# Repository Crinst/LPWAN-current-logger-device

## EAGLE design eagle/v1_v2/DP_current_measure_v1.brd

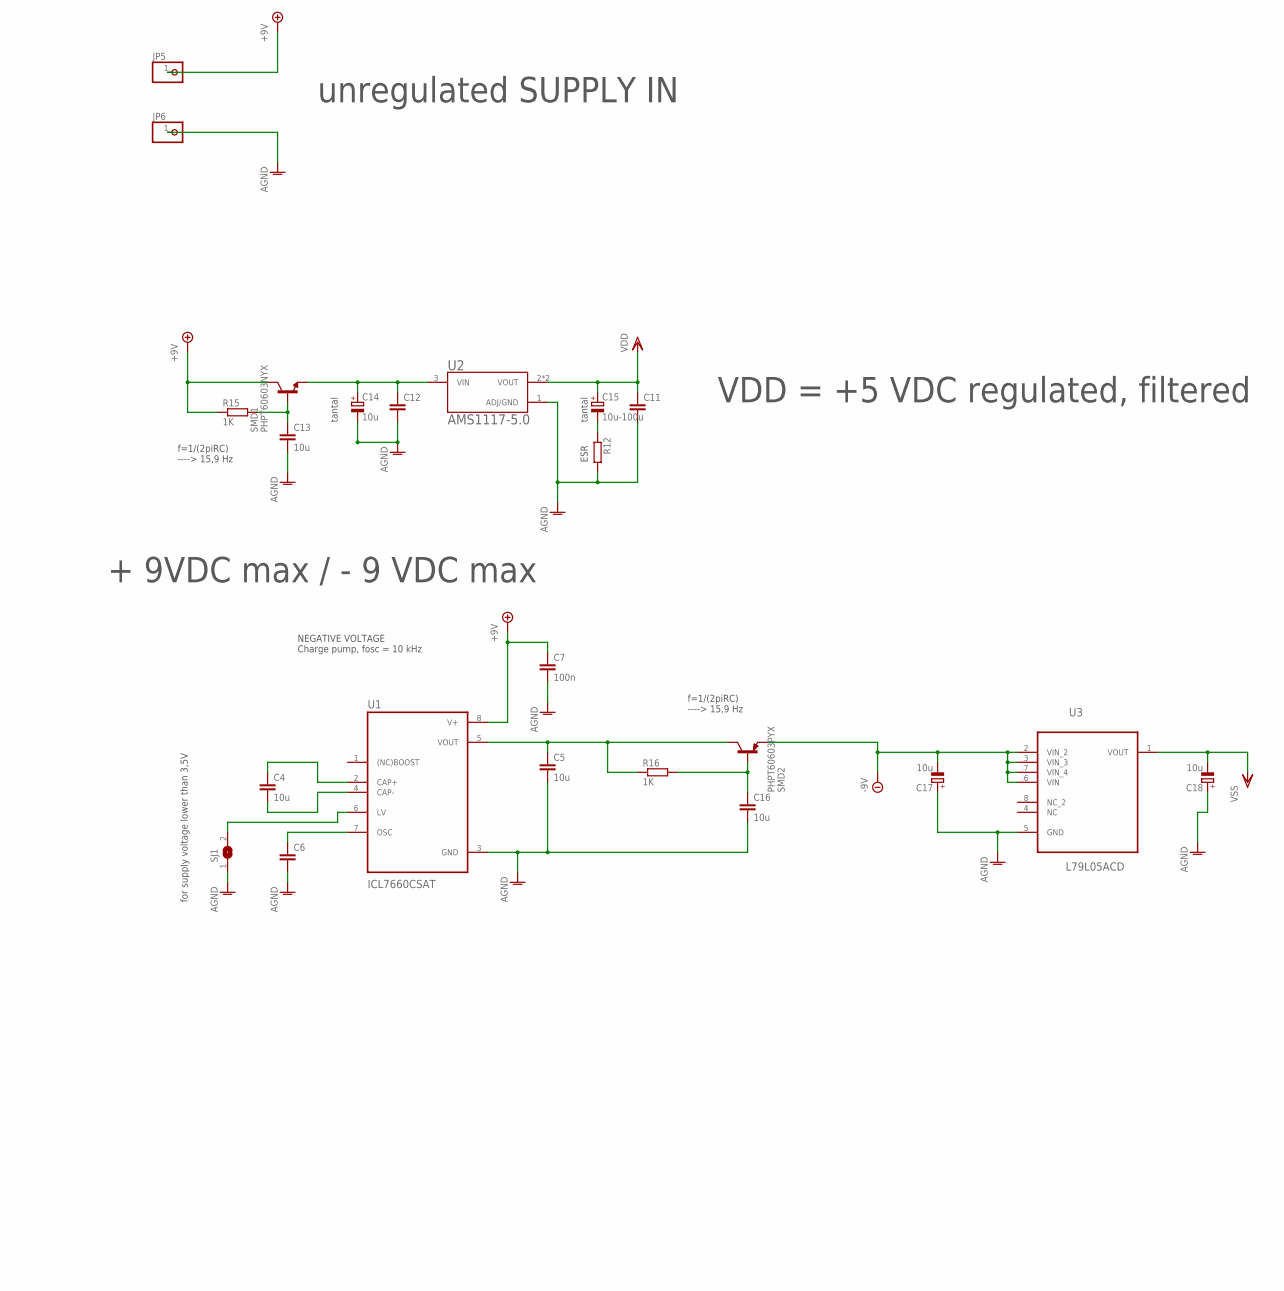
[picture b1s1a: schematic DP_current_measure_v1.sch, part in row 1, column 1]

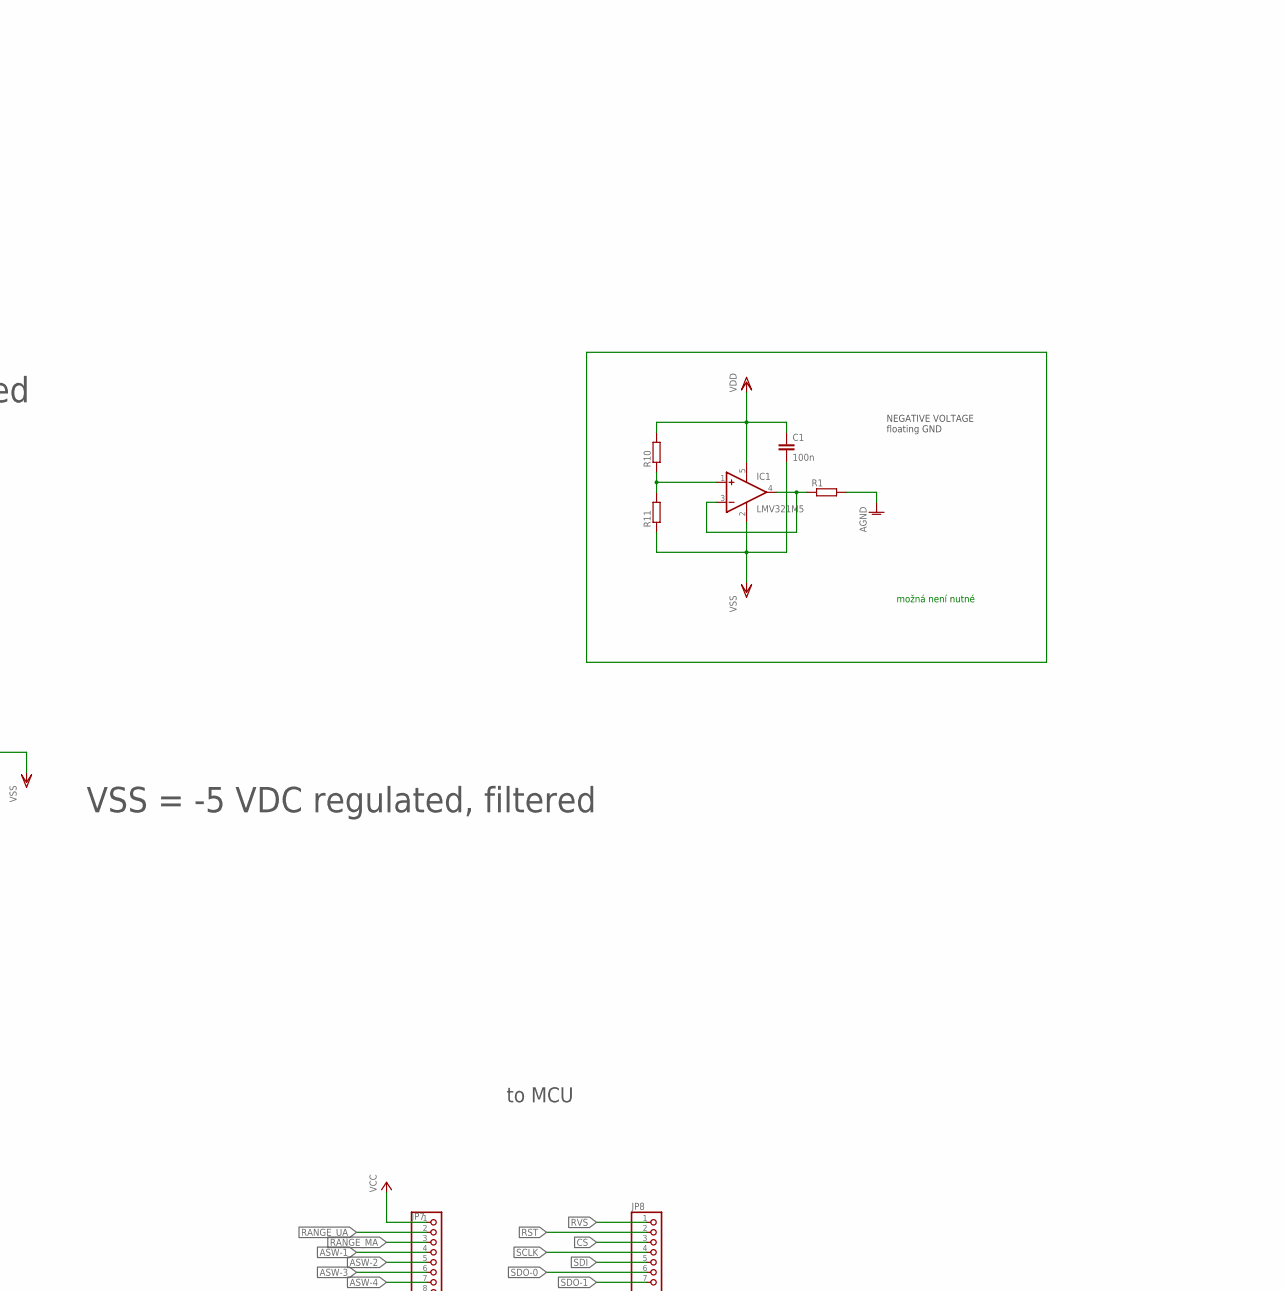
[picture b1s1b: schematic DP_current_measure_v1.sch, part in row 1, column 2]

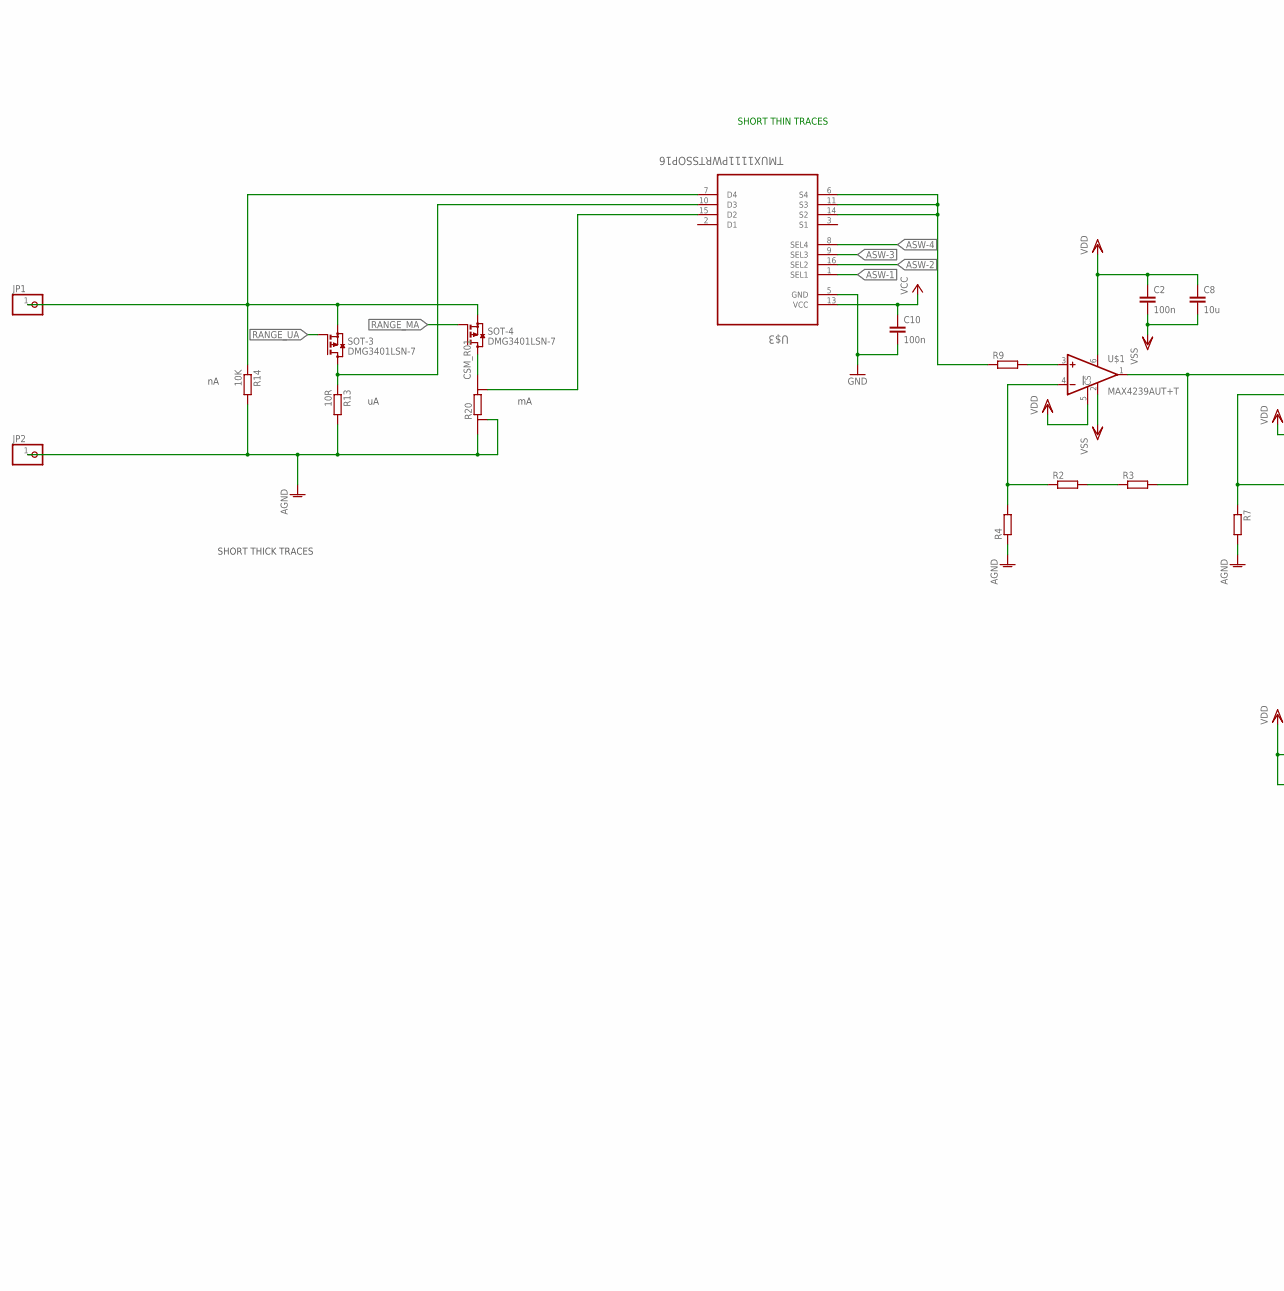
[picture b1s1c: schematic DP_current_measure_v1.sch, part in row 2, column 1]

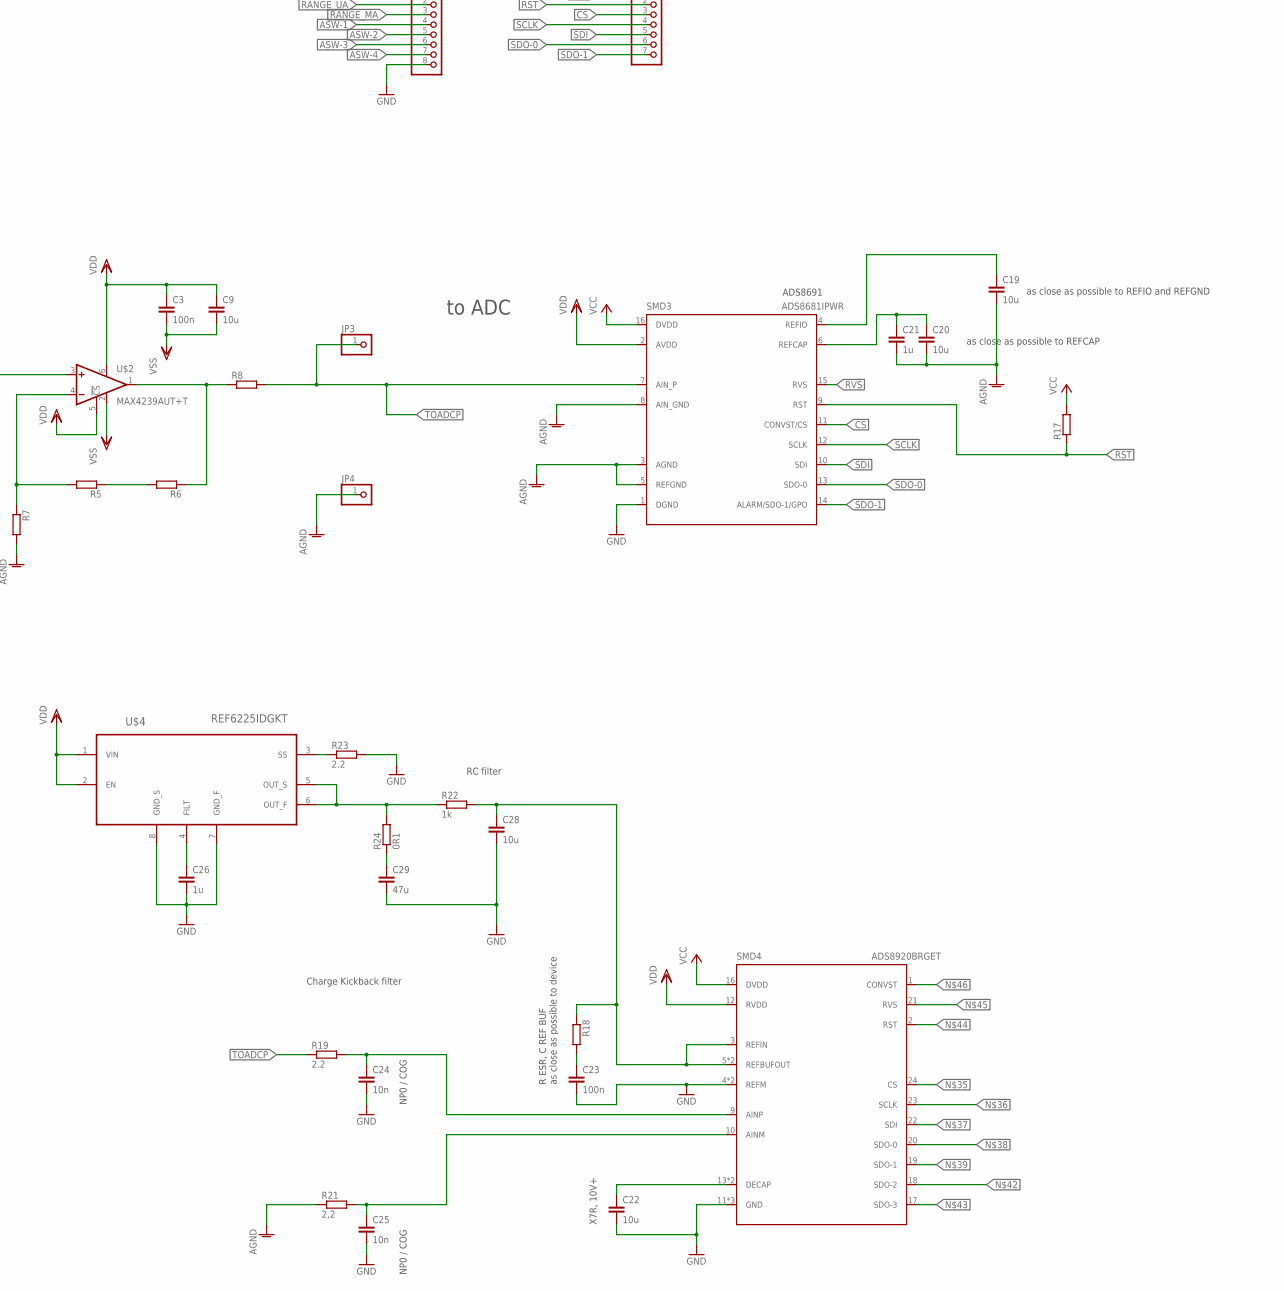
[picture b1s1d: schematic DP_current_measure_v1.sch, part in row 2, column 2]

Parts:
C1, C2, C3, C7, C10, C23: 100n; C0805
C4, C5, C8, C9, C13, C16, C19, C20, C22, C28: 10u; C1206
C6, C11, C12: C-EUC1206; C1206
C14, C17, C18: 10u; SMC_B
C15: 10u-100u; SMC_B
C21: 1u; C0805
C24, C25: 10n; C0805
C26: 1u; C1206
C29: 47u; C1206
IC1: LMV321M5; SOT23-5
JP1, JP2, JP3, JP4, JP5, JP6: PINHD-1X1; 1X01
JP7: PINHD-1X8; 1X08
JP8: PINHD-1X7; 1X07
R1, R2, R3, R4, R5, R6, R7, R8, R9, R10, R11, R12, R17, R18: R-EU_R0805; R0805
R13: 10R; R0805
R14: 10K; R0805
R15, R16: 1K; R0805
R19, R23: 2.2; R0805
R20: CSM_R01; R2512
R21: 2,2; R0805
R22: 1k; R0805
R24: 0R1; R0805
SJ1: SJ
SMD1: PHPT60603NYX; TO127P600X120-5N
SMD2: PHPT60603PYX; TO127P600X120-5N
SMD3: ADS8681IPWR; SOP65P640X120-16N
SMD4: ADS8920BRGET; BQ24195RGER
SOT-3, SOT-4: DMG3401LSN-7; SOT23
U1: ICL7660CSAT; SOIC127P600X175-8N
U2: AMS1117-5.0; SOT229P700X180-4N
U3: L79L05ACD; SOIC127P600X175-8N
U$1, U$2: MAX4239AUT+T; SOT23-6
U$3: TMUX1111PWRTSSOP16; SOP65P640X110-16N
U$4: REF6225IDGKT; SOP65P640X120-16N

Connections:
+9V: JP5.1
+12V: C7.1, R15.1, SMD1.5 (C), U1.8 (V+)
-12V: C17.-, SMD2.1 (E), SMD2.2 (E), SMD2.3 (E), U3.2 (VIN_2), U3.3 (VIN_3), U3.6 (VIN), U3.7 (VIN_4)
AGND: C5.2, C6.2, C7.2, C11.2, C12.2, C13.2, C14.-, C16.2, C17.+, C18.+, C19.2, C20.2, C21.2, JP2.1, JP4.1, JP6.1, R1.2, R4.1, R7.2, R12.2, R13.2, R14.2, R20.E1, R20.I1, R21.1, SJ1.1, SMD3.3 (AGND), SMD3.5 (REFGND), SMD3.8 (AIN_GND), U1.3 (GND), U2.1 (ADJ/GND), U3.5 (GND)
ASW-1: JP7.4, U$3.1 (SEL1)
ASW-2: JP7.5, U$3.16 (SEL2)
ASW-3: JP7.6, U$3.9 (SEL3)
ASW-4: JP7.7, U$3.8 (SEL4)
CS: JP8.3, SMD3.11 (CONVST/CS)
GND: C10.2, C22.2, C23.2, C24.2, C25.2, C26.2, C28.2, C29.2, JP7.8, R23.2, SMD3.1 (DGND), SMD4.4 (REFM), SMD4.8 (REFM), SMD4.11 (GND), SMD4.15 (GND), SMD4.25 (GND), U$3.5 (GND), U$4.7 (GND_F), U$4.8 (GND_S)
unnamed: R6.1, R8.1, U$2.1 (OUT)
unnamed: R5.1, R6.2
unnamed: R5.2, R7.1, U$2.4 (-IN)
unnamed: R2.2, R3.1
unnamed: R3.2, U$1.1 (OUT), U$2.3 (+IN)
unnamed: R9.2, U$1.3 (+IN)
unnamed: R2.1, R4.2, U$1.4 (-IN)
unnamed: R13.1, SOT-3.3 (D), U$3.10 (D3)
unnamed: IC1.3 (-IN), IC1.4 (OUT), R1.1
unnamed: IC1.1 (+IN), R10.1, R11.2
unnamed: JP1.1, R14.1, SOT-3.2 (S), SOT-4.2 (S), U$3.7 (D4)
unnamed: R22.1, R24.2, U$4.5 (OUT_S), U$4.6 (OUT_F)
unnamed: R20.E2, U$3.15 (D2)
unnamed: R9.1, U$3.6 (S4), U$3.11 (S3), U$3.14 (S2)
unnamed: C4.2, U1.4 (CAP-)
unnamed: R20.I2, SOT-4.3 (D)
unnamed: C4.1, U1.2 (CAP+)
unnamed: C6.1, U1.7 (OSC)
unnamed: C15.-, R12.1
unnamed: SJ1.2, U1.6 (LV)
unnamed: C12.1, C14.+, SMD1.1 (E), SMD1.2 (E), SMD1.3 (E), U2.3 (VIN)
unnamed: C13.1, R15.2, SMD1.4 (B)
unnamed: C5.1, R16.1, SMD2.5 (C), U1.5 (VOUT)
unnamed: C16.1, R16.2, SMD2.4 (B)
unnamed: C23.1, R18.2
unnamed: C24.1, R19.2, SMD4.9 (AINP)
unnamed: C28.1, R18.1, R22.2, SMD4.3 (REFIN), SMD4.5 (REFBUFOUT), SMD4.7 (REFBUFOUT)
unnamed: C29.1, R24.1
unnamed: C26.1, U$4.4 (FILT)
unnamed: C25.1, R21.2, SMD4.10 (AINM)
unnamed: C22.1, SMD4.13 (DECAP), SMD4.14 (DECAP)
unnamed: R23.1, U$4.3 (SS)
unnamed: C20.1, C21.1, SMD3.6 (REFCAP)
unnamed: C19.1, SMD3.4 (REFIO)
RANGE_MA: JP7.3, SOT-4.1 (G)
RANGE_UA: JP7.2, SOT-3.1 (G)
RST: JP8.2, R17.1, SMD3.9 (RST)
RVS: JP8.1, SMD3.15 (RVS)
SCLK: JP8.4, SMD3.12 (SCLK)
SDI: JP8.5, SMD3.10 (SDI)
SDO-0: JP8.6, SMD3.13 (SDO-0)
SDO-1: JP8.7, SMD3.14 (ALARM/SDO-1/GPO)
TOADCP: JP3.1, R8.2, R19.1, SMD3.7 (AIN_P)
VCC: C10.1, JP7.1, R17.2, SMD3.16 (DVDD), SMD4.16 (DVDD), U$3.13 (VCC)
VDD: C1.1, C2.1, C3.1, C8.1, C9.1, C11.1, C15.+, IC1.5 (V+), R10.2, SMD3.2 (AVDD), SMD4.12 (RVDD), U2.2 (VOUT), U2.4 (VOUT), U$1.5 (!CS), U$1.6 (V+), U$2.5 (!CS), U$2.6 (V+), U$4.1 (VIN), U$4.2 (EN)
VSS: C1.2, C2.2, C3.2, C8.2, C9.2, C18.-, IC1.2 (V-), R11.1, U3.1 (VOUT), U$1.2 (V-), U$2.2 (V-)

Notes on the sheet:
NEGATIVE VOLTAGE floating GND
možná není nutné
SHORT THICK TRACES
SHORT THIN TRACES
unregulated SUPPLY IN
for supply voltage lower than 3,5V
NEGATIVE VOLTAGE Charge pump, fosc = 10 kHz
to MCU
to ADC
tantal
ESR
f=1/(2piRC) ----> 15,9 Hz
+ 9VDC max / - 9 VDC max
VDD = +5 VDC regulated, filtered
VSS = -5 VDC regulated, filtered
as close as possible to REFIO and REFGND
as close as possible to REFCAP
X7R, 10V+
R ESR, C REF BUF as close as possible to device
NP0 / COG
Charge Kickback filter
ADS8691
RC filter

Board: 2 copper layers, 75 parts (0 on the bottom side), 55 nets, no tracks yet.

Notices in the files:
parts and their libraries:
Wurth_Elektronik_Electromechanic_Input-O: Copyright: Würth Elektronik
